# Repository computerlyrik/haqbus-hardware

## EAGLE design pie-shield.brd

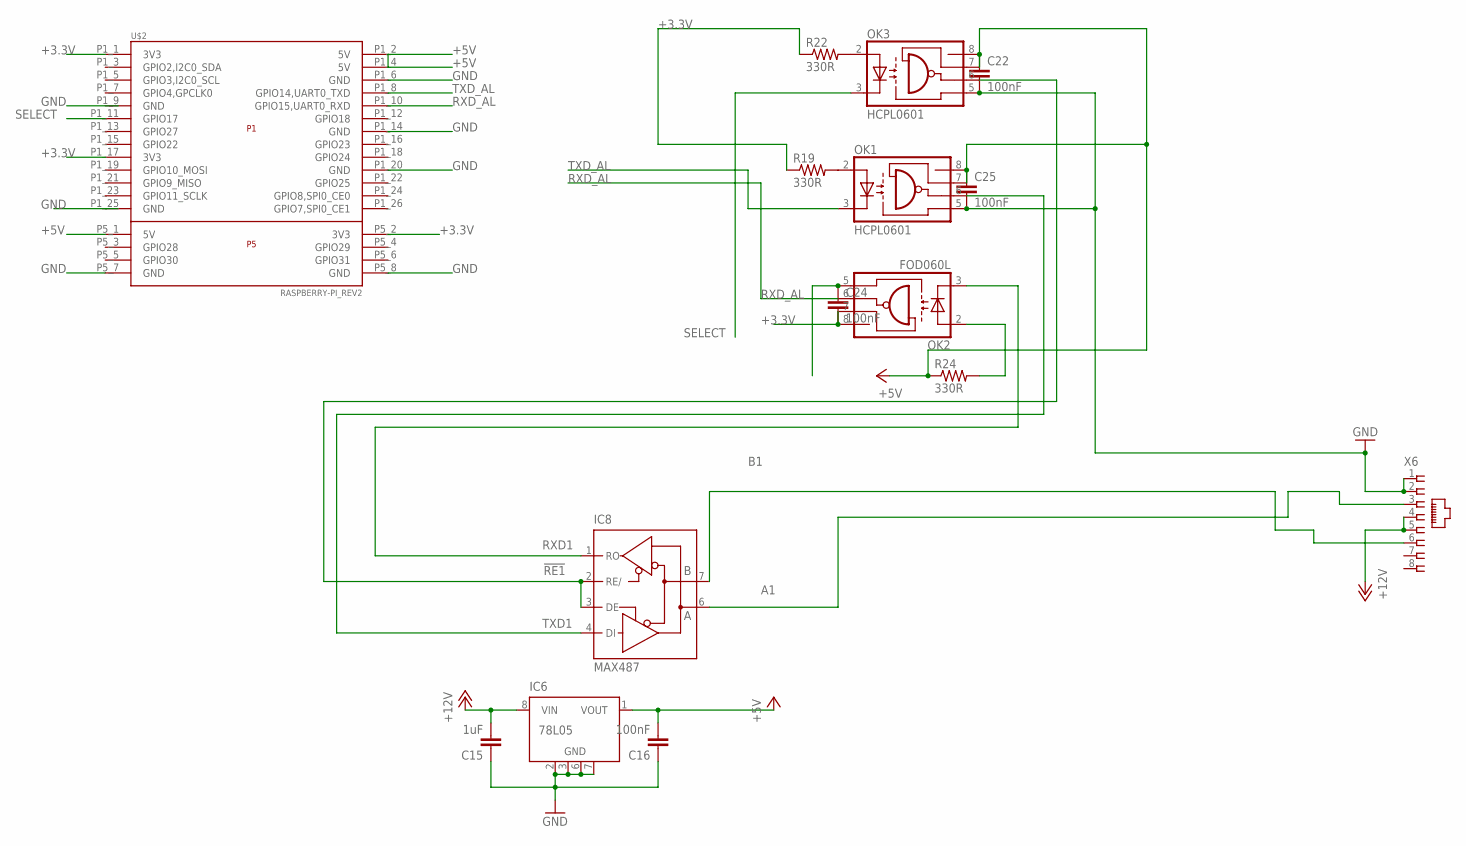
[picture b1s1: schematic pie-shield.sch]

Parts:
C15: 1uF; 0805
C16, C22, C24, C25: 100nF; 0805
IC6: 78L05; SO08
IC8: MAX487; SO08
OK1, OK3: HCPL0601; SOIC08
OK2: FOD060L; SOIC08
R19, R22, R24: 330R; 0805
U$2: RASPBERRY-PI_REV2
X6: RJ45-8L-B; RJ45-NO-SHIELD

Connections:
!RE1: IC8.2 (RE/), IC8.3 (DE), OK3.6 (VO)
+3.3V: C24.2, OK2.7 (VE), OK2.8 (VCC), R19.1, R22.1, U$2.P1_1 (3V3), U$2.P1_17 (3V3), U$2.P5_2 (3V3)
+5V: U$2.P1_2 (5V), U$2.P1_4 (5V), U$2.P5_1 (5V)
+5V1: C16.2, C22.1, C25.1, IC6.1 (VOUT), OK1.7 (VE), OK1.8 (VCC), OK3.7 (VE), OK3.8 (VCC), R24.1
+24V: C15.2, IC6.8 (VIN), X6.4, X6.5
A1: IC8.6 (A), X6.3
B1: IC8.7 (B), X6.6
GND: C24.1, OK2.5 (GND), U$2.P1_6 (GND), U$2.P1_14 (GND), U$2.P1_20 (GND), U$2.P5_7 (GND), U$2.P5_8 (GND)
GND_AL: C15.1, C16.1, C22.2, C25.2, IC6.2 (GND), IC6.3 (GND), IC6.6 (GND), IC6.7 (GND), IC8.5 (GND), OK1.5 (GND), OK3.5 (GND), X6.1, X6.2
unnamed: OK1.2 (A), R19.2
unnamed: OK2.2 (A), R24.2
unnamed: OK3.2 (A), R22.2
RXD1: IC8.1 (RO), OK2.3 (C)
RXD_AL: OK2.6 (VO), U$2.P1_10 (GPIO15,UART0_RXD)
SELECT: OK3.3 (C), U$2.P1_11 (GPIO17)
TXD1: IC8.4 (DI), OK1.6 (VO)
TXD_AL: OK1.3 (C), U$2.P1_8 (GPIO14,UART0_TXD)
VCC: IC8.8 (VCC)

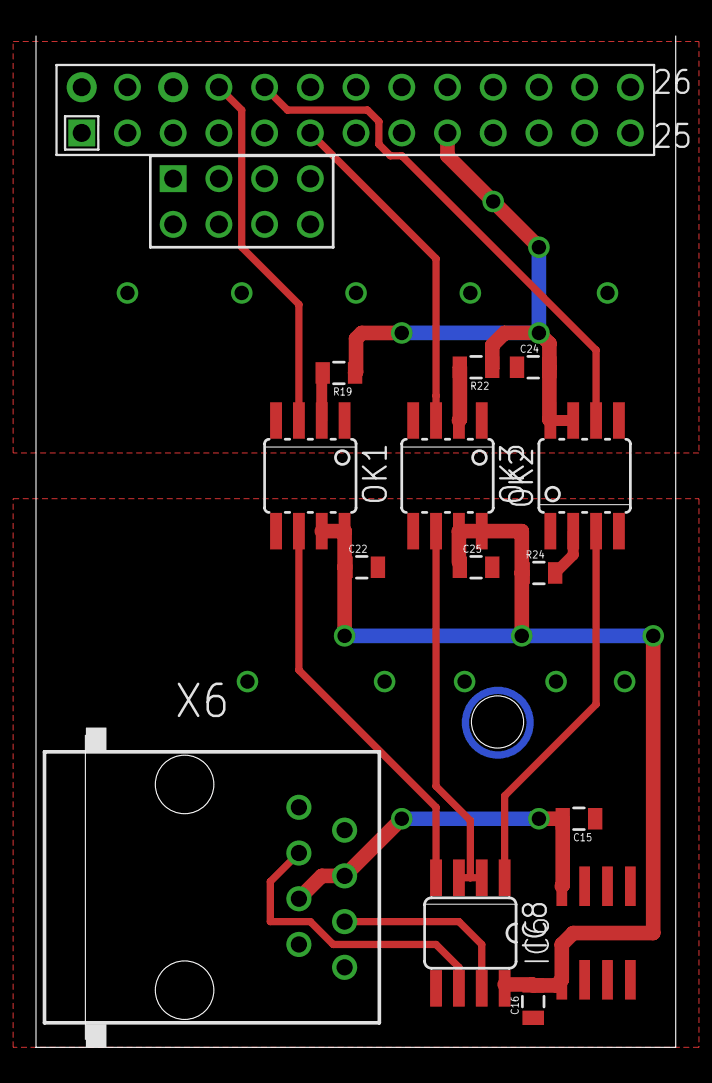
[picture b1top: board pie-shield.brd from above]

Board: 2 copper layers, 35.5 x 56.2 mm, 15 parts (0 on the bottom side), 17 nets.

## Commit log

2013-02-05 initial
2013-02-05 before wiring to raspberry
2013-02-05 wired
2013-02-05 1 layered
2013-02-05 one-layerd with ground-bridges
2013-02-05 using uart pins
2013-02-05 rewired to use uart txd, rxd and rts
2013-02-06 set optocouplers on pie side to 3.3V levels
